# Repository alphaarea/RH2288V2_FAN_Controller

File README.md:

# RH2288V2 FAN Controller
**RH2288V2 风扇控制器**

Base on Arduino

Limit the annoying fan speed, made it possible to be a quite homeserver.

## Compatibility
- Huawei Tecal RH2285 V2
- Huawei Tecal RH2285H V2
- Huawei Tecal RH2288 V2
- Huawei Tecal RH2288H V2

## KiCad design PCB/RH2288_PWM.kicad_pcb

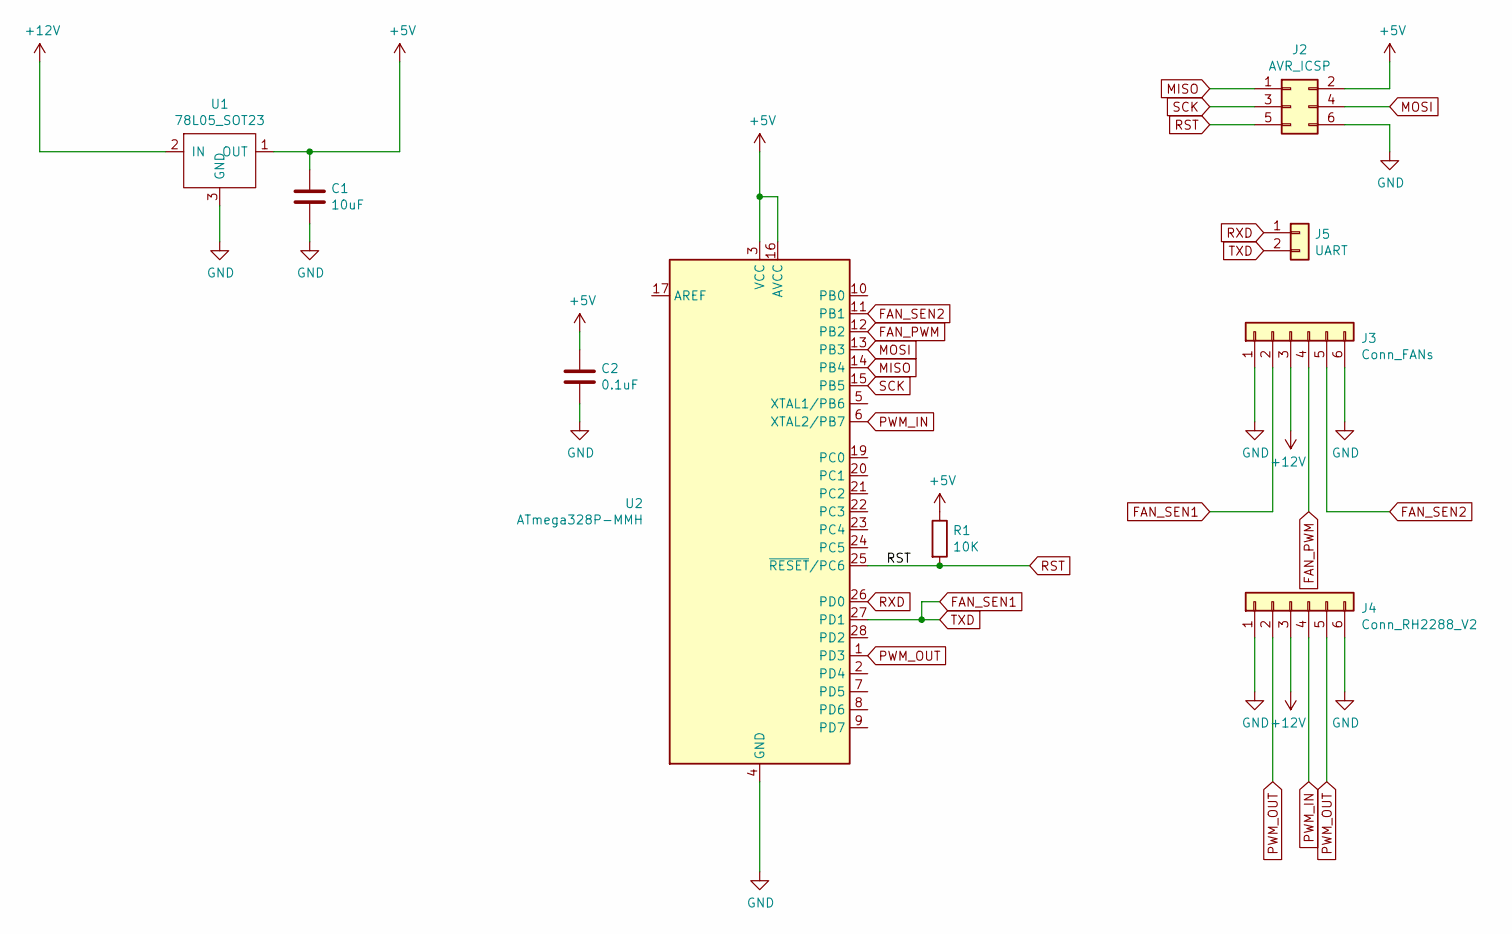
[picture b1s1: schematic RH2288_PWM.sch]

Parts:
C1: 10uF; C_0603_1608Metric
C2: 0.1uF; C_0603_1608Metric
J2: AVR_ICSP; PinHeader_2x03_P2.54mm_Vertical
J3: Conn_FANs; PinHeader_1x06_P2.54mm_Horizontal
J4: Conn_RH2288_V2; PinSocket_1x06_P2.54mm_Horizontal
J5: UART; PinHeader_1x02_P2.54mm_Vertical
R1: 10K; R_0603_1608Metric
U1: 78L05_SOT23; SOT-23
U2: ATmega328P-MMH; QFN-28-1EP_4x4mm_P0.45mm_EP2.4x2.4mm

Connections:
+5V: C1.1, C2.1, J2.2, R1.1, U1.1 (OUT), U2.3 (VCC), U2.16 (AVCC)
+12V: J3.3, J4.3, U1.2 (IN)
FAN_PWM: J3.4, U2.12 (PB2)
FAN_SEN1: J3.2, J5.2, U2.27 (PD1)
FAN_SEN2: J3.5, U2.11 (PB1)
GND: C1.2, C2.2, J2.6, J3.1, J3.6, J4.1, J4.6, U1.3 (GND), U2.4 (GND), U2.18 (GND), U2.29 (GND)
MISO: J2.1, U2.14 (PB4)
MOSI: J2.4, U2.13 (PB3)
PWM_IN: J4.4, U2.6 (XTAL2/PB7)
PWM_OUT: J4.2, J4.5, U2.1 (PD3)
RST: J2.5, R1.2, U2.25 (~RESET~/PC6)
RXD: J5.1, U2.26 (PD0)
SCK: J2.3, U2.15 (PB5)

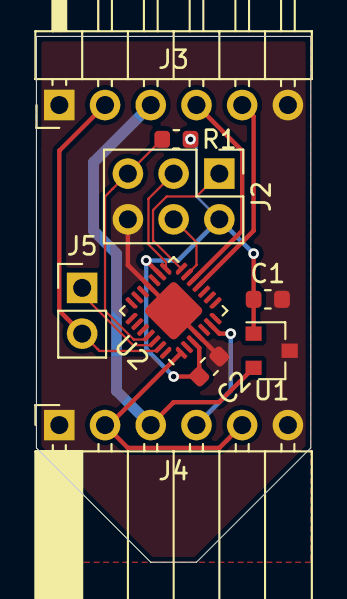
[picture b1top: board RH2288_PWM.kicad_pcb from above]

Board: 2 copper layers, 15.2 x 29.2 mm, 9 parts (0 on the bottom side), 13 nets.

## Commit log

2020-03-19 Create repo
2020-03-25 PCB finished
